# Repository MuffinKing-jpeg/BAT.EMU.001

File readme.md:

# BAT.UME.001

This is dummy battery.

## Elements

- Emulates ESR with two  resistors (2516)
- MLCC (0805) for transients handling
- Aluminum caps (6.3mm) for bulk capacity
- Bleed resistors array (0805)
- Potentiometer (WDX3) for emulating thermistor

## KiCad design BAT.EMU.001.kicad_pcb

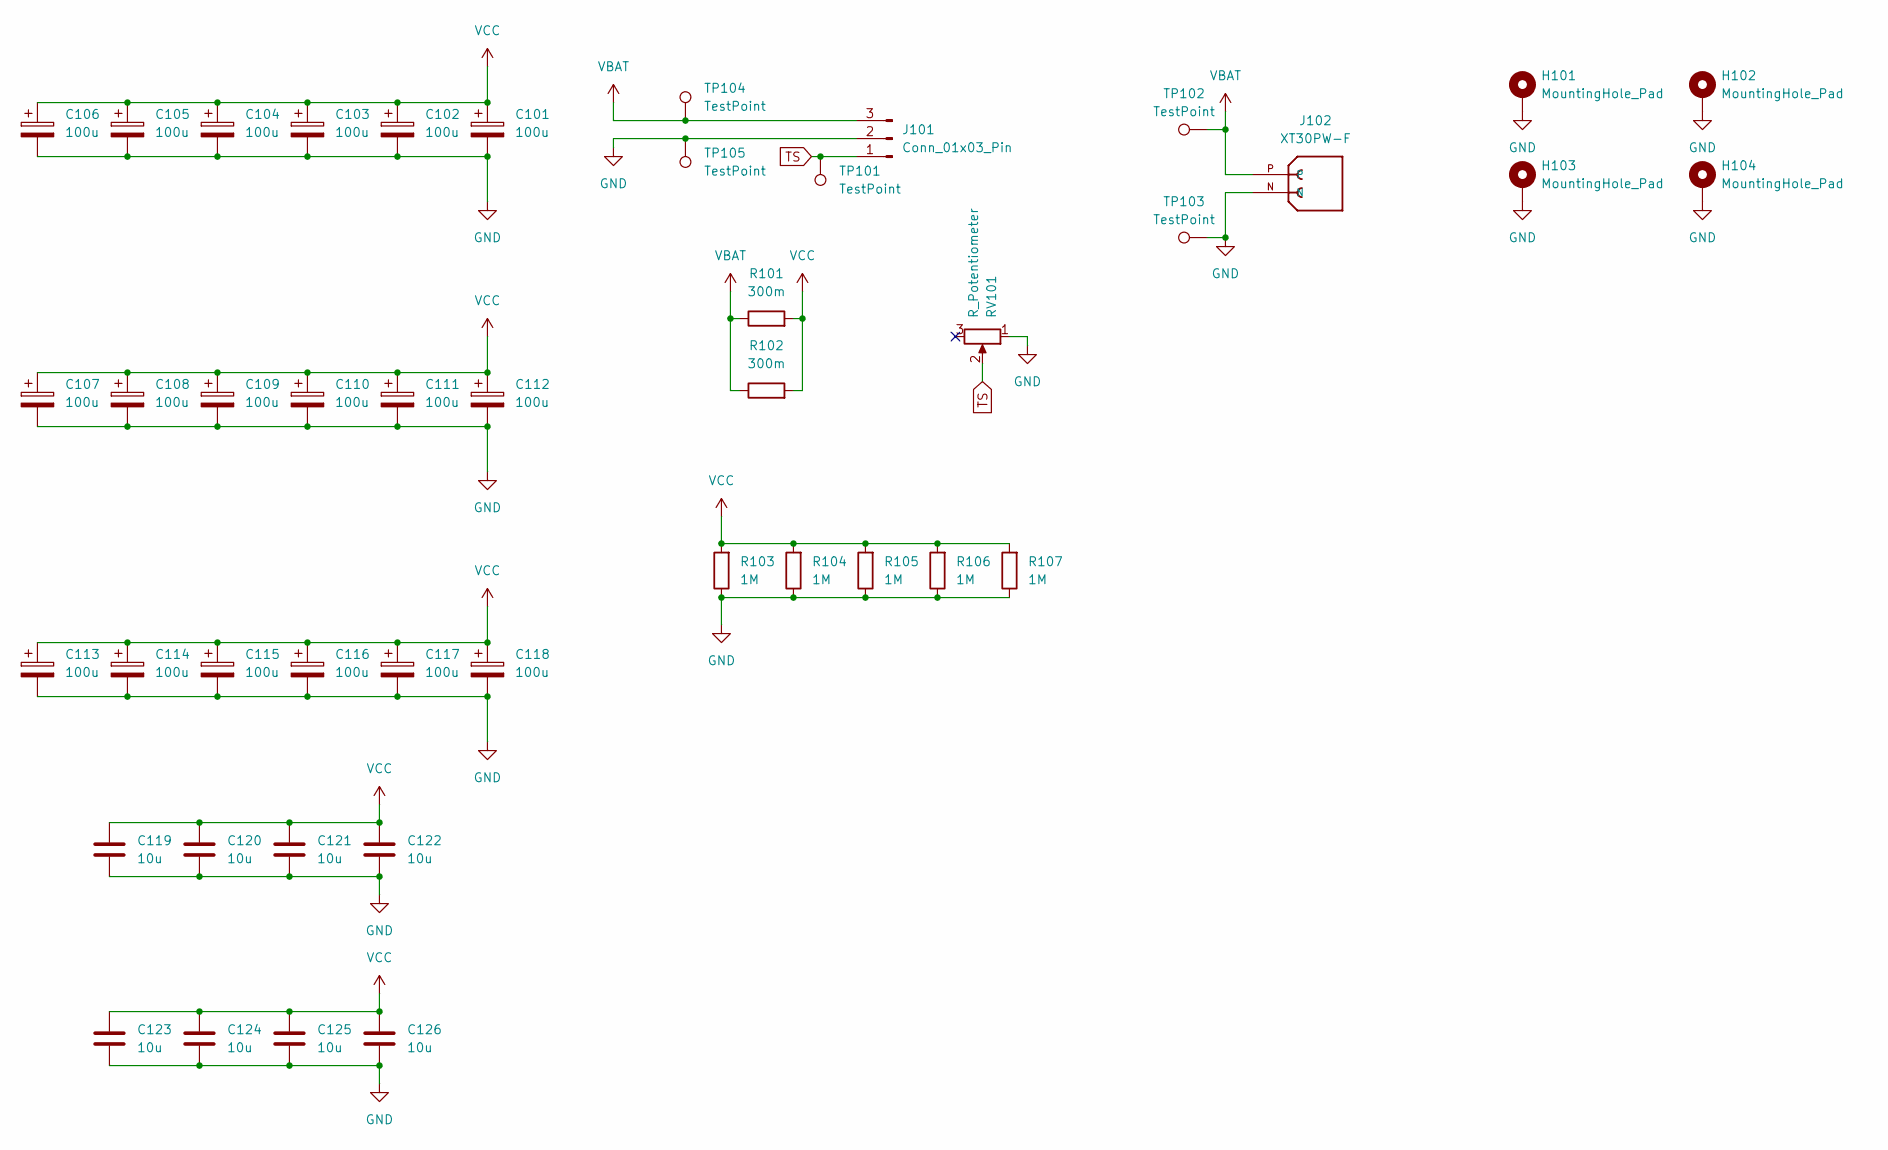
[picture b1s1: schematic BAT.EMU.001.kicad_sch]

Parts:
C101, C102, C103, C104, C105, C106, C107, C108, C109, C110, C111, C112, C113, C114, C115, C116, C117, C118: 100u; CP_Elec_6.3x5.4
C119, C120, C121, C122, C123, C124, C125, C126: 10u; C_0805_2012Metric
H101, H102, H103, H104: MountingHole_Pad; MountingHole_3.2mm_M3_ISO7380_Pad
J101: Conn_01x03_Pin; JST_PH_S3B-PH-K_1x03_P2.00mm_Horizontal
J102: XT30PW-F; AMASS_XT30PW-F; PARTREV 1.2
R101, R102: 300m; R_2512_6332Metric
R103, R104, R105, R106, R107: 1M; R_0805_2012Metric
RV101: R_Potentiometer; WXD3-13
TP101, TP102, TP103: TestPoint; TestPoint_Pad_D1.5mm
TP104, TP105: TestPoint; TestPoint_Bridge_Pitch2.54mm_Drill0.7mm

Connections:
GND: C101.2, C102.2, C103.2, C104.2, C105.2, C106.2, C107.2, C108.2, C109.2, C110.2, C111.2, C112.2, C113.2, C114.2, C115.2, C116.2, C117.2, C118.2, C119.2, C120.2, C121.2, C122.2, C123.2, C124.2, C125.2, C126.2, H101.1, H102.1, H103.1, H104.1, J101.2, J102.N, R103.1, R104.1, R105.1, R106.1, R107.1, RV101.1, TP103.1, TP105.1
TS: J101.1, RV101.2, TP101.1
VBAT: J101.3, J102.P, R101.1, R102.1, TP102.1, TP104.1
VCC: C101.1, C102.1, C103.1, C104.1, C105.1, C106.1, C107.1, C108.1, C109.1, C110.1, C111.1, C112.1, C113.1, C114.1, C115.1, C116.1, C117.1, C118.1, C119.1, C120.1, C121.1, C122.1, C123.1, C124.1, C125.1, C126.1, R101.2, R102.2, R103.2, R104.2, R105.2, R106.2, R107.2

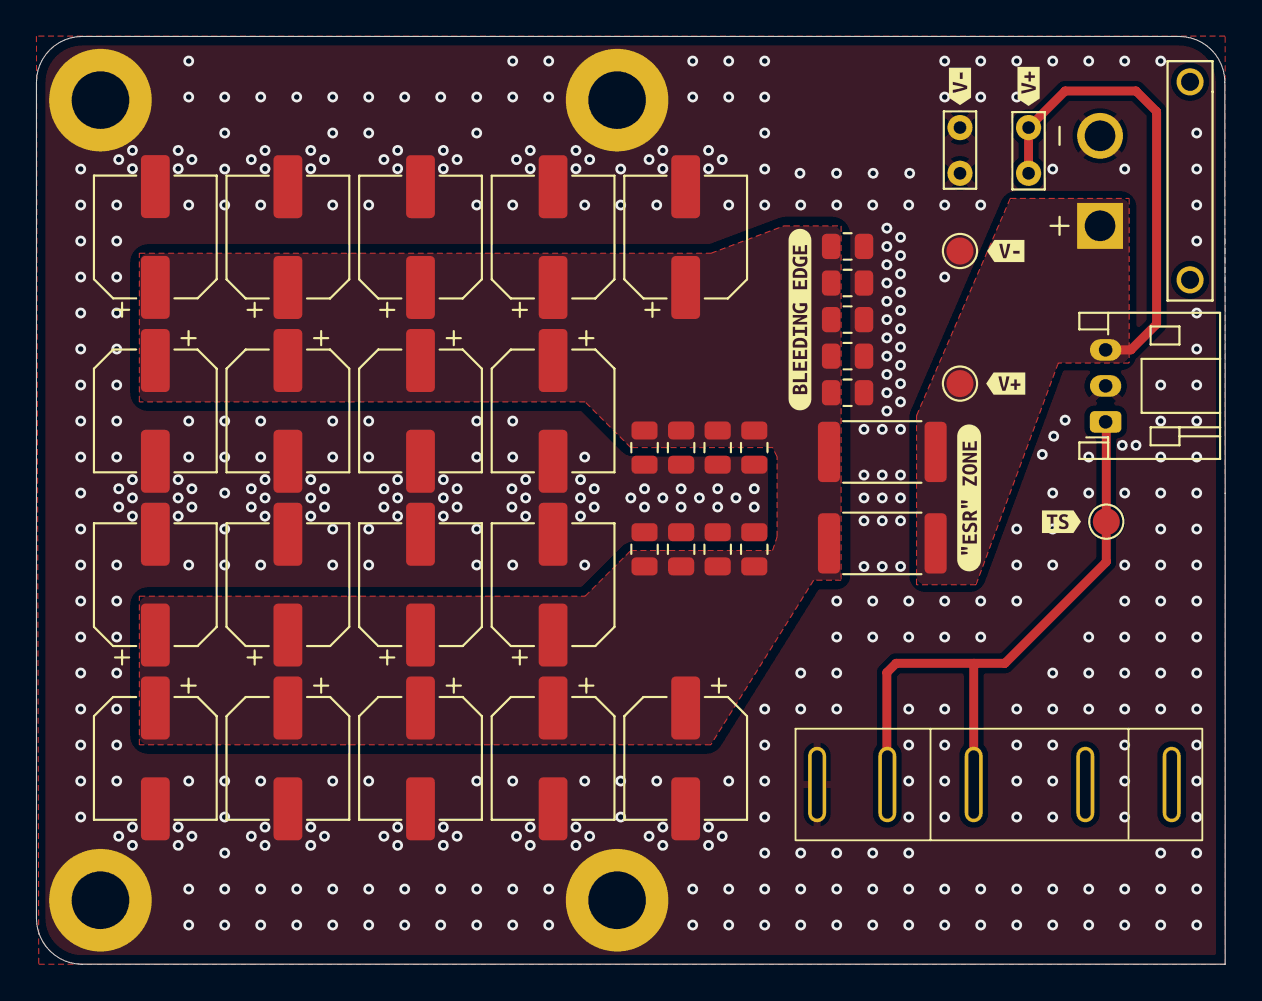
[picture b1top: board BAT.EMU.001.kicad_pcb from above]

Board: 2 copper layers, 66.0 x 51.5 mm, 54 parts (0 on the bottom side), 4 nets.

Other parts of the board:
kibuzzard-67A7E40D: G***; kibuzzard-67A7E40D
kibuzzard-67A7E497: G***; kibuzzard-67A7E497
kibuzzard-67A87EB1: G***; kibuzzard-67A87EB1
kibuzzard-67A87EE2: G***; kibuzzard-67A87EE2
kibuzzard-67A881B4: G***; kibuzzard-67A881B4
kibuzzard-67A881D8, kibuzzard-67A881D8#2: G***; kibuzzard-67A881D8
kibuzzard-67A881E3, kibuzzard-67A881E3#2: G***; kibuzzard-67A881E3

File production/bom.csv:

Designator,Footprint,Quantity,Value,LCSC Part #
"C101, C102, C103, C104, C105, C106, C107, C108, C109, C110, C111, C112, C113, C114, C115, C116, C117, C118",CP_Elec_6.3x5.4,18,100u,
"C119, C120, C121, C122, C123, C124, C125, C126",0805,8,10u,
J101,JST_PH_S3B-PH-K_1x03_P2.00mm_Horizontal,1,Conn_01x03_Pin,
J102,AMASS_XT30PW-F,1,XT30PW-F,
"R101, R102",2512,2,300m,
"R103, R104, R105, R106, R107",0805,5,1M,
RV101,WXD3-13,1,R_Potentiometer,
"TP101, TP102, TP103",TestPoint_Pad_D1.5mm,3,TestPoint,
"TP104, TP105",TestPoint_Bridge_Pitch2.54mm_Drill0.7mm,2,TestPoint,

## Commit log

2025-02-09 Fixed fatal issue (label was little off)
